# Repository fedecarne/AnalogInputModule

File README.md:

This is the repo of the Analog Input Module for Bpod.

This repository contains:

-Firmware for Arduino
-Software API for MATLAB
-Design files for the circuit board
-Design files for the enclosure

Requirements:

- ArCOM (https://github.com/sanworks/ArCOM)

Features:

- Arduino-compatible 180MHz ARM Cortex M4 processor (Teensy 3.6)
- 8 x 12 bit Analog inputs (based on Analog Devices AD7327BRUZ)
- Sampling rate: up to 100kHz (1 channel)
- Voltage range settings: -10V:10V, -5V:5V, -2.5V:2.5V, 0V:10V
- 8GB microSD memory for data storage and retrieval
- 2 UART connections to communicate threshold-crossing events to state machine
- Online streaming of digitalized signal through USB or UART
- MATLAB API for easy configuration and usage during behavioral experiments

To get started:
1. Add this folder 'MATLAB' to the MATLAB path.

2. Create your BpodAnalogIn object (you might need to specify the serial port)

	Ain = BpodAnalogIn('COM14');

3. Run Analog Streamer:

	Ain.Streamer

Check out the [documentation](https://sites.google.com/site/bpodanaloginmodule/analog-input-module).

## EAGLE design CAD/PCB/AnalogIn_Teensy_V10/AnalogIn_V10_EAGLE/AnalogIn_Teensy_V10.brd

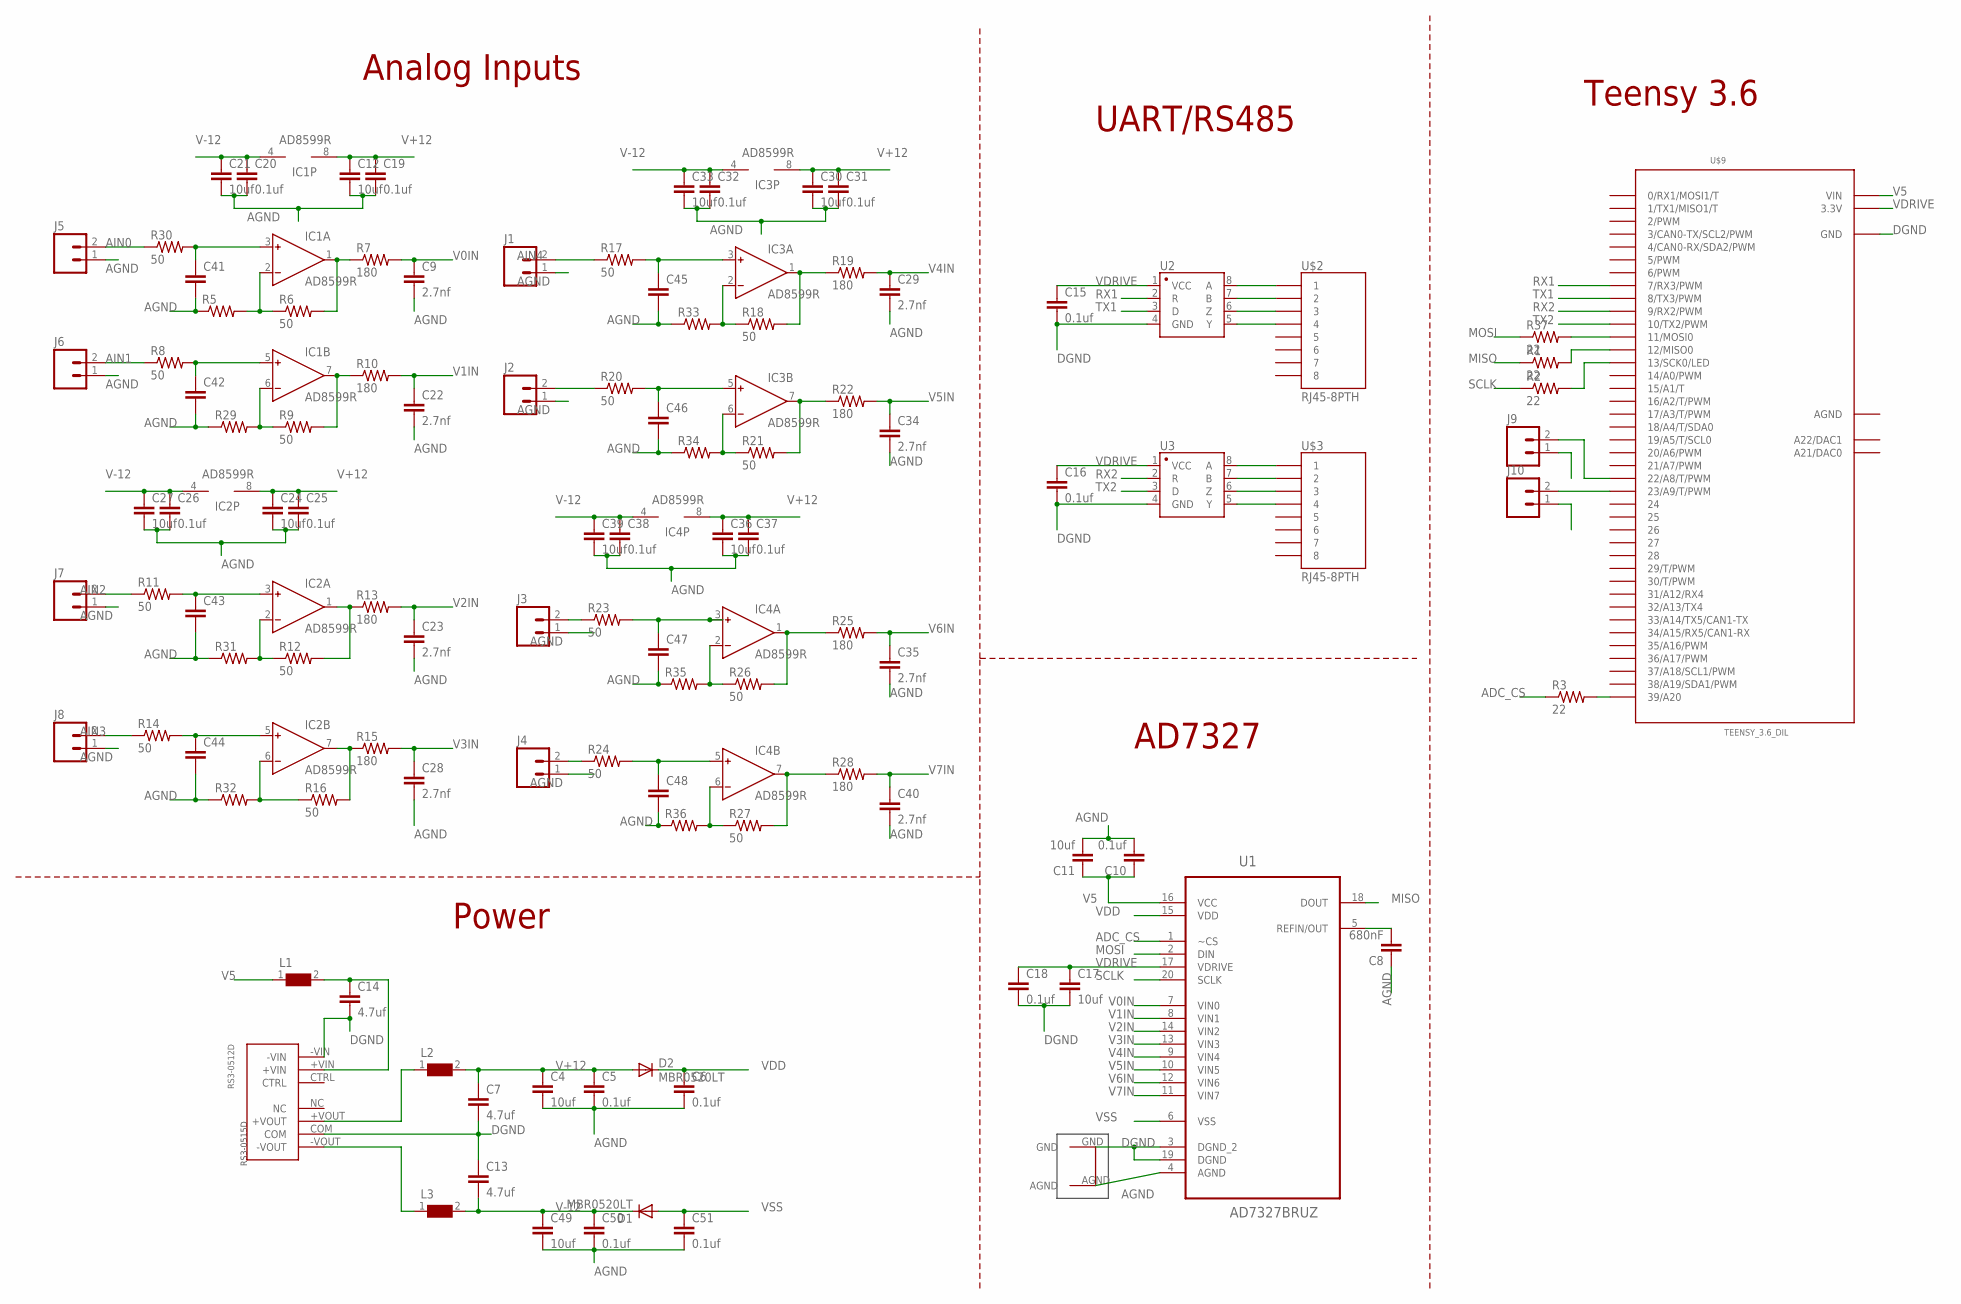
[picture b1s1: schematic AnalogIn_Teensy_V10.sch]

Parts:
C4, C11, C12, C17, C21, C24, C27, C30, C33, C36, C39, C49: 10uf; 0603-CAP
C5, C6, C10, C15, C16, C18, C19, C20, C25, C26, C31, C32, C37, C38, C50, C51: 0.1uf; 0603-CAP
C7, C13, C14: 4.7uf; 0603-CAP
C8: 680nF; 0603-CAP
C9, C22, C23, C28, C29, C34, C35, C40: 2.7nf; 0603-CAP
C41, C42, C43, C44, C45, C46, C47, C48: CAP0603-CAP; 0603-CAP
D1, D2: MBR0520LT; SOD123
IC1, IC2, IC3, IC4: AD8599R; SO8
J1, J2, J3, J4, J5, J6, J7, J8, J9, J10: M023.5MM; SCREWTERMINAL-3.5MM-2
L1, L2, L3: WE-CBF-742792118_1206; 1206
R1, R2, R3, R37: 22; 0603-RES
R5, R29, R31, R32, R33, R34, R35, R36: RESISTOR0603; 0603-RES
R6, R8, R9, R11, R12, R14, R16, R17, R18, R20, R21, R23, R24, R26, R27, R30: 50; 0603-RES
R7, R10, R13, R15, R19, R22, R25, R28: 180; 0603-RES
RS3-0512D: RS3-0515D
U1: AD7327BRUZ; SOP65P640X120-20N
U2, U3: SN65HVD31DR; SO08
U$2, U$3: RJ45-8PTH; RJ45-8
U$4: GNDPLANESHRT
U$9: TEENSY_3.6_DIL

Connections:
+VOUT: L2.1, RS3-0512D.+VOUT
-VOUT: L3.1, RS3-0512D.-VOUT
ADC_CS: R3.1, U1.1 (~CS)
AGND: C4.2, C5.2, C6.2, C8.1, C9.2, C10.2, C11.2, C12.2, C19.2, C20.2, C21.2, C22.2, C23.2, C24.2, C25.2, C26.2, C27.2, C28.2, C29.2, C30.2, C31.2, C32.2, C33.2, C34.2, C35.2, C36.2, C37.2, C38.2, C39.2, C40.2, C41.2, C42.2, C43.2, C44.2, C45.2, C46.2, C47.2, C48.2, C49.2, C50.2, C51.2, J1.1, J2.1, J3.1, J4.1, J5.1, J6.1, J7.1, J8.1, R5.1, R29.1, R31.1, R32.1, R33.1, R34.1, R35.1, R36.1, U1.4 (AGND), U$4.AGND, U$9.AGND
AIN0: J5.2, R30.1
AIN1: J6.2, R8.1
AIN2: J7.2, R11.1
AIN3: J8.2, R14.1
AIN4: J1.2, R17.1
AIN5: J2.2, R20.1
AIN6: J3.2, R23.1
AIN7: J4.2, R24.1
DGND: C7.2, C13.1, C14.2, C15.2, C16.2, C17.2, C18.2, J9.1, J10.1, RS3-0512D.-VIN, RS3-0512D.COM, U1.3 (DGND_2), U1.19 (DGND), U2.4 (GND), U3.4 (GND), U$4.GND, U$9.GND, U$9.GND1 (GND)
MISO: R1.1, U1.18 (DOUT)
MOSI: R37.1, U1.2 (DIN)
unnamed: U2.6 (Z), U$2.3
unnamed: U2.8 (A), U$2.1
unnamed: U2.5 (Y), U$2.4
unnamed: U2.7 (B), U$2.2
unnamed: U3.6 (Z), U$3.3
unnamed: U3.5 (Y), U$3.4
unnamed: U3.8 (A), U$3.1
unnamed: U3.7 (B), U$3.2
unnamed: R37.2, U$9.11 (11/MOSI0)
unnamed: R1.2, U$9.12 (12/MISO0)
unnamed: C14.1, L1.2, RS3-0512D.+VIN
unnamed: R3.2, U$9.39/A20
unnamed: C41.1, IC1.3 (IN+), R30.2
unnamed: R2.2, U$9.13 (13/SCK0/LED)
unnamed: IC1.2 (IN-), R5.2, R6.1
unnamed: IC1.1 (OUT), R6.2, R7.1
unnamed: J10.2, U$9.23/A9 (23/A9/T/PWM)
unnamed: J9.2, U$9.22/A8 (22/A8/T/PWM)
unnamed: C42.1, IC1.5 (IN+), R8.2
unnamed: IC1.6 (IN-), R9.1, R29.2
unnamed: IC1.7 (OUT), R9.2, R10.1
unnamed: C43.1, IC2.3 (IN+), R11.2
unnamed: IC2.2 (IN-), R12.1, R31.2
unnamed: IC2.1 (OUT), R12.2, R13.1
unnamed: C44.1, IC2.5 (IN+), R14.2
unnamed: IC2.6 (IN-), R16.1, R32.2
unnamed: IC2.7 (OUT), R15.1, R16.2
unnamed: C45.1, IC3.3 (IN+), R17.2
unnamed: IC3.2 (IN-), R18.1, R33.2
unnamed: IC3.1 (OUT), R18.2, R19.1
unnamed: C46.1, IC3.5 (IN+), R20.2
unnamed: IC3.6 (IN-), R21.1, R34.2
unnamed: IC3.7 (OUT), R21.2, R22.1
unnamed: C47.1, IC4.3 (IN+), R23.2
unnamed: IC4.2 (IN-), R26.1, R35.2
unnamed: IC4.1 (OUT), R25.1, R26.2
unnamed: C48.1, IC4.5 (IN+), R24.2
unnamed: IC4.6 (IN-), R27.1, R36.2
unnamed: IC4.7 (OUT), R27.2, R28.1
REF: C8.2, U1.5 (REFIN/OUT)
RX1: U2.2 (R), U$9.7 (7/RX3/PWM)
RX2: U3.2 (R), U$9.9 (9/RX2/PWM)
SCLK: R2.1, U1.20 (SCLK)
TX1: U2.3 (D), U$9.8 (8/TX3/PWM)
TX2: U3.3 (D), U$9.10 (10/TX2/PWM)
V0IN: C9.1, R7.2, U1.7 (VIN0)
V1IN: C22.1, R10.2, U1.8 (VIN1)
V2IN: C23.1, R13.2, U1.14 (VIN2)
V3IN: C28.1, R15.2, U1.13 (VIN3)
V4IN: C29.1, R19.2, U1.9 (VIN4)
V5: C10.1, C11.1, L1.1, U1.16 (VCC), U$9.VIN
V5IN: C34.1, R22.2, U1.10 (VIN5)
V6IN: C35.1, R25.2, U1.12 (VIN6)
V7IN: C40.1, R28.2, U1.11 (VIN7)
V+12: C4.1, C5.1, C7.1, C12.1, C19.1, C24.1, C25.1, C30.1, C31.1, C36.1, C37.1, D2.A, IC1.8 (V+), IC2.8 (V+), IC3.8 (V+), IC4.8 (V+), L2.2
V-12: C13.2, C20.1, C21.1, C26.1, C27.1, C32.1, C33.1, C38.1, C39.1, C49.1, C50.1, D1.C, IC1.4 (V-), IC2.4 (V-), IC3.4 (V-), IC4.4 (V-), L3.2
VDD: C6.1, D2.C, U1.15 (VDD)
VDRIVE: C15.1, C16.1, C17.1, C18.1, U1.17 (VDRIVE), U2.1 (VCC), U3.1 (VCC), U$9.3.3V, U$9.3.3V3 (3.3V)
VSS: C51.1, D1.A, U1.6 (VSS)

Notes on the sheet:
Teensy 3.6
UART/RS485
AD7327
Analog Inputs
Power

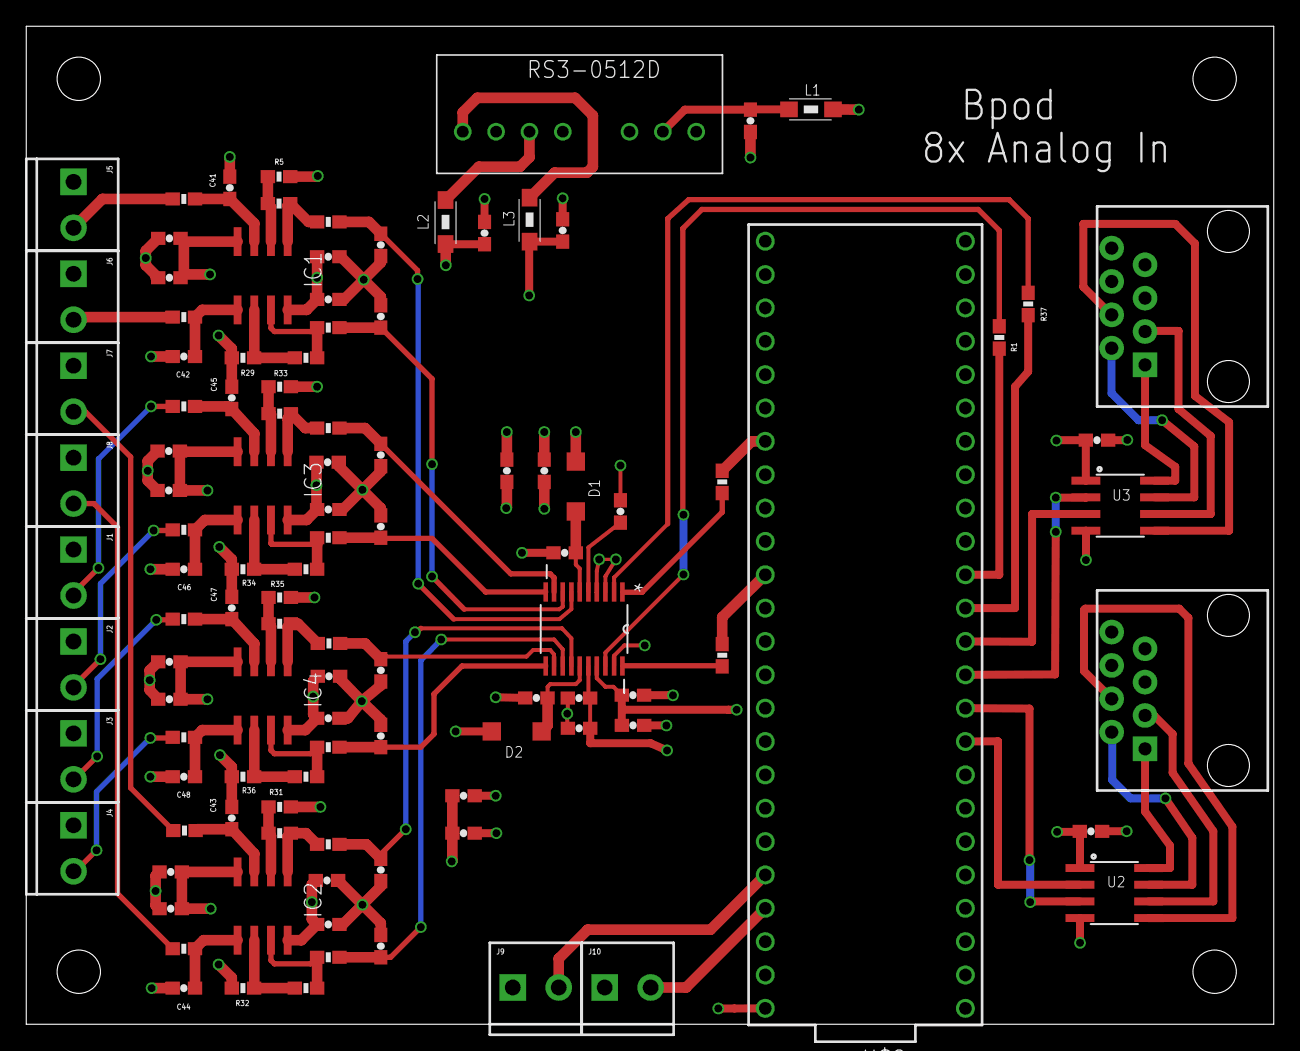
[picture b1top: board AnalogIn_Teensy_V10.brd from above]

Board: 4 copper layers, 95.0 x 76.0 mm, 115 parts (0 on the bottom side), 74 nets.

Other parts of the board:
U$5, U$6, U$7, U$8: STAND-OFF

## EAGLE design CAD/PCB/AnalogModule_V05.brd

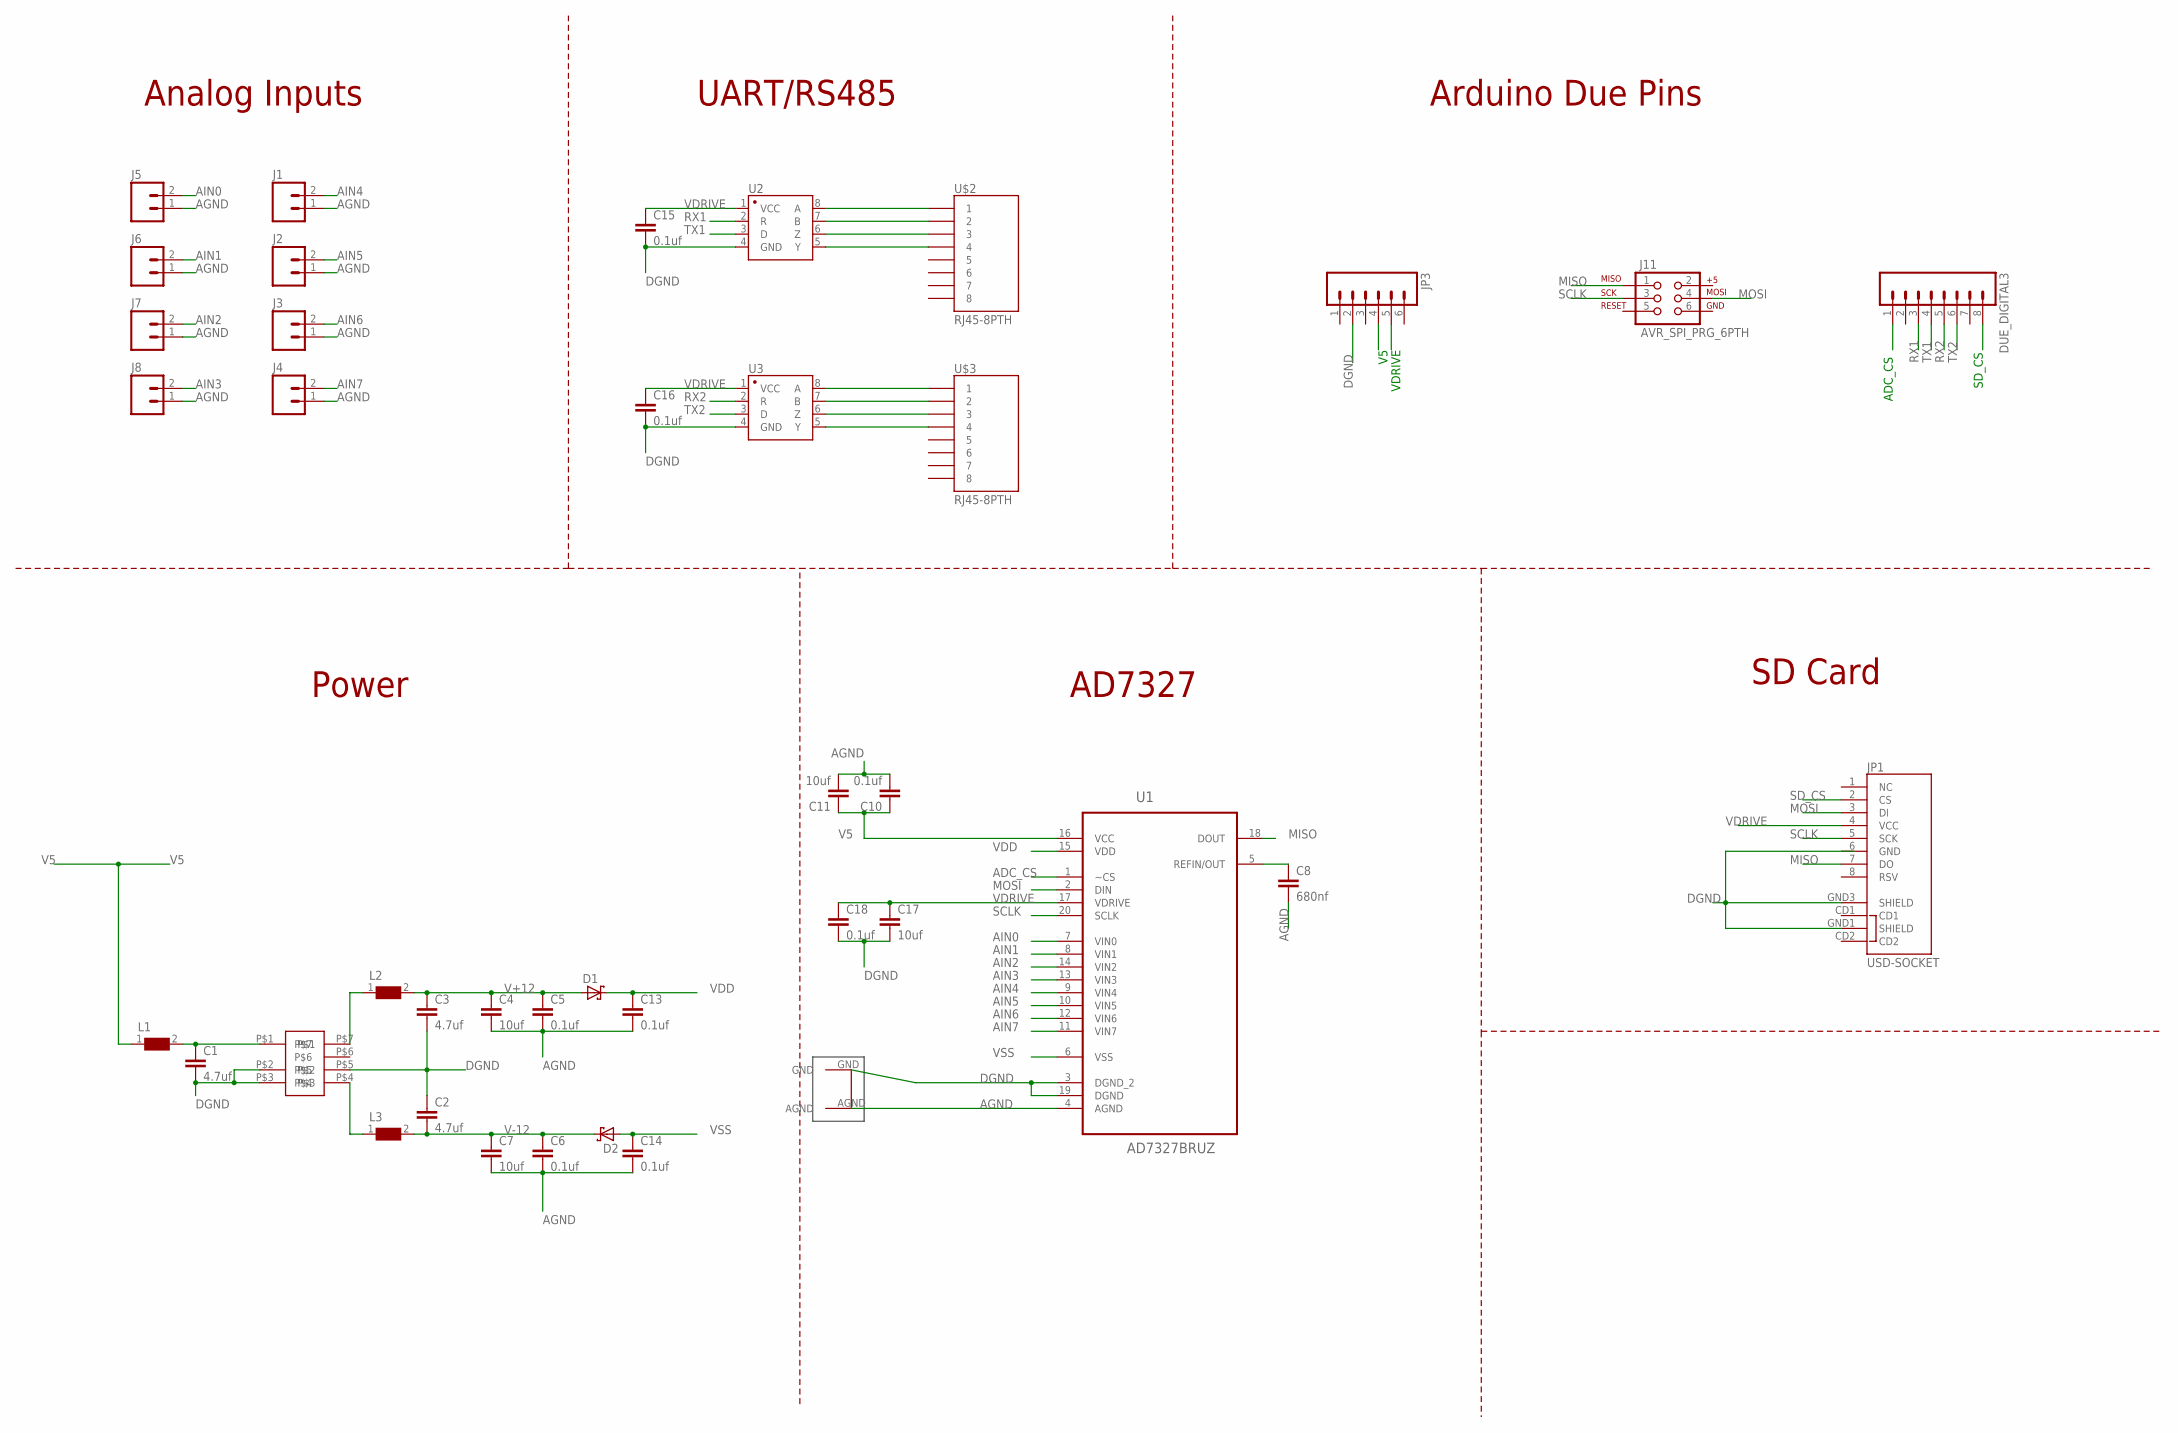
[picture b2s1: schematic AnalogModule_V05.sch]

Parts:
C1, C2, C3: 4.7uf; 1206
C4, C7: 10uf; 1206
C5, C6, C13, C14: 0.1uf; 1206
C8: 680nf; 1206
C10, C15, C16, C18: 0.1uf; 0603-CAP
C11, C17: 10uf; 0603-CAP
D1, D2: SCHOTTKY-DIODESMD; SMB
DUE_DIGITAL3: M081X08; 1X08
J1, J2, J3, J4, J5, J6, J7, J8: M023.5MM; SCREWTERMINAL-3.5MM-2
J11: AVR_SPI_PRG_6PTH; 2X3
JP1: USD-SOCKET; MICROSD_1:1
JP3: M06SILK_FEMALE_PTH; 1X06
L1, L2, L3: WE-CBF-742792118_1206; 1206
U1: AD7327BRUZ; SOP65P640X120-20N
U2, U3: SN65HVD31DR; SO08
U$1: TDK_LAMBDA_5_TO_BI_12_125MA
U$2, U$3: RJ45-8PTH; RJ45-8
U$4: GNDPLANESHRT

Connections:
ADC_CS: DUE_DIGITAL3.1, U1.1 (~CS)
AGND: C4.2, C5.2, C6.2, C7.2, C8.2, C10.2, C11.2, C13.2, C14.2, J1.1, J2.1, J3.1, J4.1, J5.1, J6.1, J7.1, J8.1, U1.4 (AGND), U$4.AGND
AIN0: J5.2, U1.7 (VIN0)
AIN1: J6.2, U1.8 (VIN1)
AIN2: J7.2, U1.14 (VIN2)
AIN3: J8.2, U1.13 (VIN3)
AIN4: J1.2, U1.9 (VIN4)
AIN5: J2.2, U1.10 (VIN5)
AIN6: J3.2, U1.12 (VIN6)
AIN7: J4.2, U1.11 (VIN7)
DGND: C1.2, C2.1, C3.2, C15.2, C16.2, C17.2, C18.2, JP1.GND1 (SHIELD), JP1.GND3 (SHIELD), JP3.2, U1.3 (DGND_2), U1.19 (DGND), U2.4 (GND), U3.4 (GND), U$1.P$2, U$1.P$3, U$1.P$5, U$4.GND
MISO: J11.1, JP1.7 (DO), U1.18 (DOUT)
MOSI: J11.4, JP1.3 (DI), U1.2 (DIN)
unnamed: U2.6 (Z), U$2.3
unnamed: U2.8 (A), U$2.1
unnamed: U2.5 (Y), U$2.4
unnamed: U2.7 (B), U$2.2
unnamed: U3.6 (Z), U$3.3
unnamed: U3.5 (Y), U$3.4
unnamed: U3.8 (A), U$3.1
unnamed: U3.7 (B), U$3.2
unnamed: C1.1, L1.2, U$1.P$1
unnamed: L2.1, U$1.P$7
unnamed: L3.1, U$1.P$4
REF: C8.1, U1.5 (REFIN/OUT)
RX1: DUE_DIGITAL3.3, U2.2 (R)
RX2: DUE_DIGITAL3.5, U3.2 (R)
SCLK: J11.3, JP1.5 (SCK), U1.20 (SCLK)
SD_CS: DUE_DIGITAL3.8, JP1.2 (CS)
TX1: DUE_DIGITAL3.4, U2.3 (D)
TX2: DUE_DIGITAL3.6, U3.3 (D)
V5: C10.1, C11.1, JP3.4, L1.1, U1.16 (VCC)
V+12: C3.1, C4.1, C5.1, D1.A, L2.2
V-12: C2.2, C6.1, C7.1, D2.C, L3.2
VDD: C13.1, D1.C, U1.15 (VDD)
VDRIVE: C15.1, C16.1, C17.1, C18.1, JP1.4 (VCC), JP3.5, U1.17 (VDRIVE), U2.1 (VCC), U3.1 (VCC)
VSS: C14.1, D2.A, U1.6 (VSS)

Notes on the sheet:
Arduino Due Pins
UART/RS485
SD Card
AD7327
Analog Inputs
Power
ADC_CS
VDRIVE
SD_CS

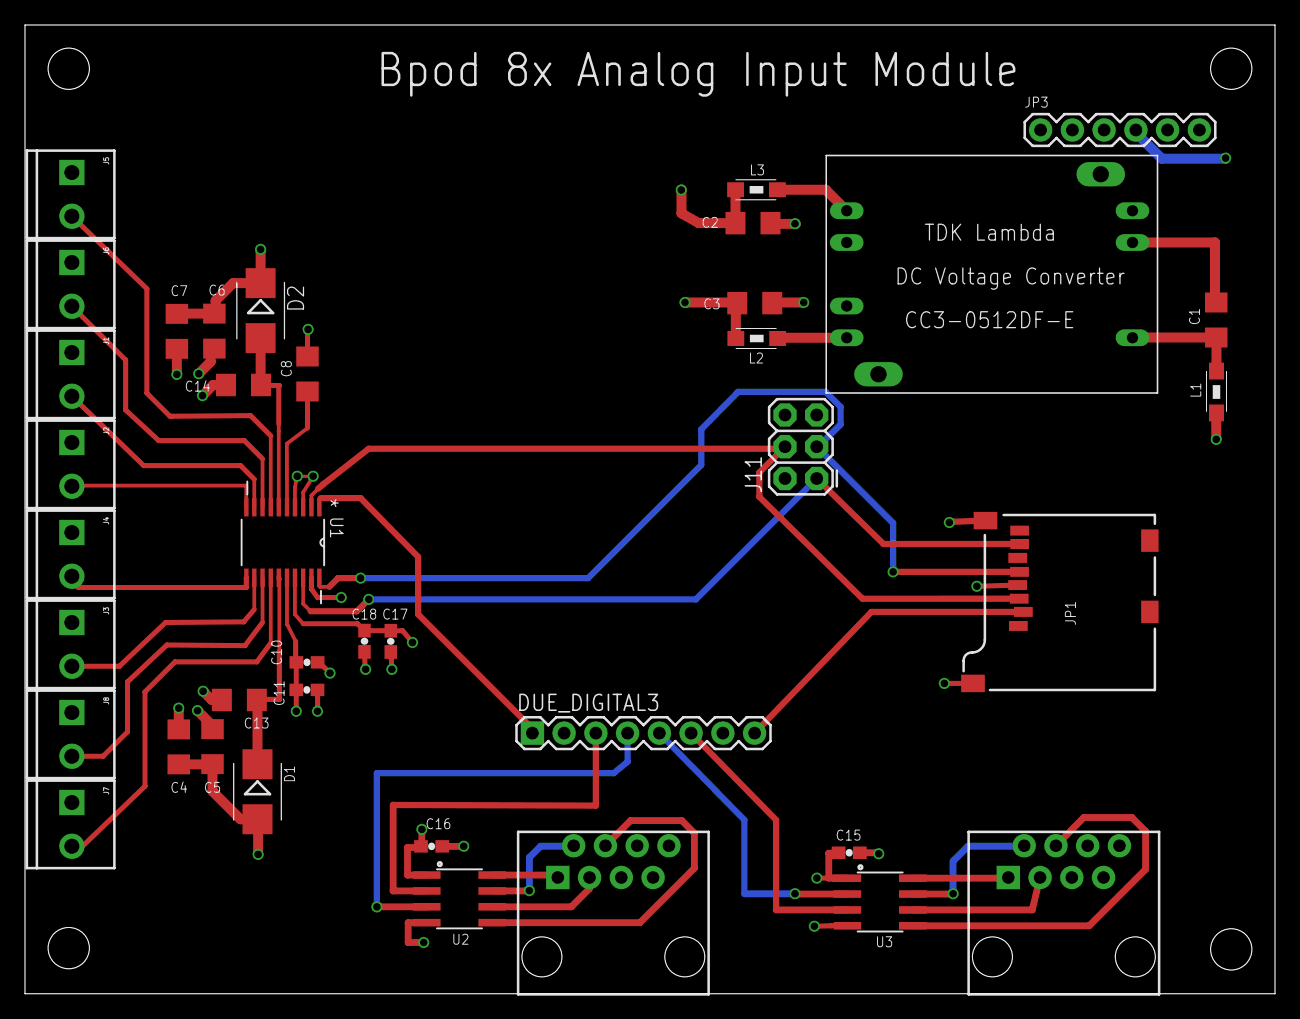
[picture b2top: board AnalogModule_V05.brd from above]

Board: 4 copper layers, 100.0 x 77.5 mm, 44 parts (0 on the bottom side), 37 nets.

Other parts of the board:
U$5, U$6, U$7, U$8: STAND-OFF

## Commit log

2017-01-16 Added files from local computer to repo.
2017-01-16 Updated readme file.
2017-01-16 Added firmware files.
2017-01-16 Add accessory functions.
2017-01-19 Added rev1 board test firmware. No SD functionality
2017-01-23 Added testing code
2017-01-24 Updated testings.
2017-01-25 Set theme jekyll-theme-minimal
2017-01-25 Added docs/
2017-01-25 Created index.html
2017-01-25 Update site
2017-01-25 Update docs/
2017-01-25 Testing site
2017-01-25 Updated site
2017-01-25 Update :)
2017-01-27 Teensy design and OOP Matlab code
2017-01-30 Teensy version with signal conditioning
2017-02-06 Update TeensyV10 board
2017-02-07 Update Teensy verion
2017-02-08 Teensy board
2017-02-08 Matlab object
2017-02-09 updated oo streamer
2017-02-10 Updated testing
2017-02-22 Teensy
2017-03-27 Testing
2017-03-28 Updated V2 with hardware
2017-05-14 orginized folders
2017-05-14 Fix small bugs
2017-05-14 updated Example 1
2017-05-14 Readme
2017-05-14 Updated Example2
2017-05-14 Fixed bugs in Example2
2017-05-14 Fixed SPI speed and retrieve function
2017-05-15 Firmware V05
2017-05-15 Fix small bugs in retrieve function
2017-05-18 Josh's changes
    - retrieving schema
    - firmware
    - voltage range attribute
    - etc
2017-05-20 -Fixed module name length data type in firmware
2017-05-22 -Rewrote AD7327 library. Major changes: uses bitSet, bitClear and bitGet methods to set register bits (for clarity at the expense of speed), uses spi.write16 to write 16-bit ints (for speed), uses 1-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

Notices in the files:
parts and their libraries:
SparkFun-Capacitors: Licensing: Creative Commons ShareAlike 4.0 International - https://creativecommons.org/licenses/by-sa/4.0
